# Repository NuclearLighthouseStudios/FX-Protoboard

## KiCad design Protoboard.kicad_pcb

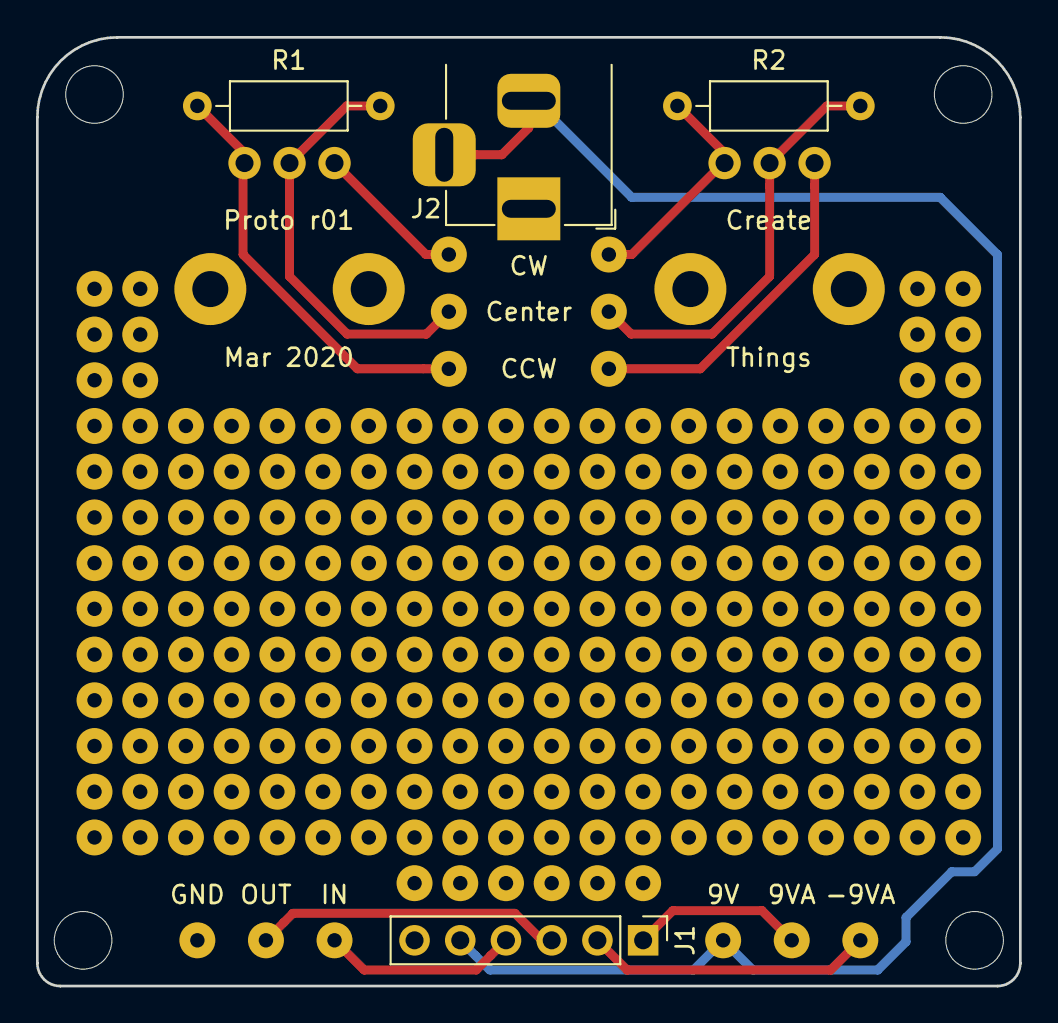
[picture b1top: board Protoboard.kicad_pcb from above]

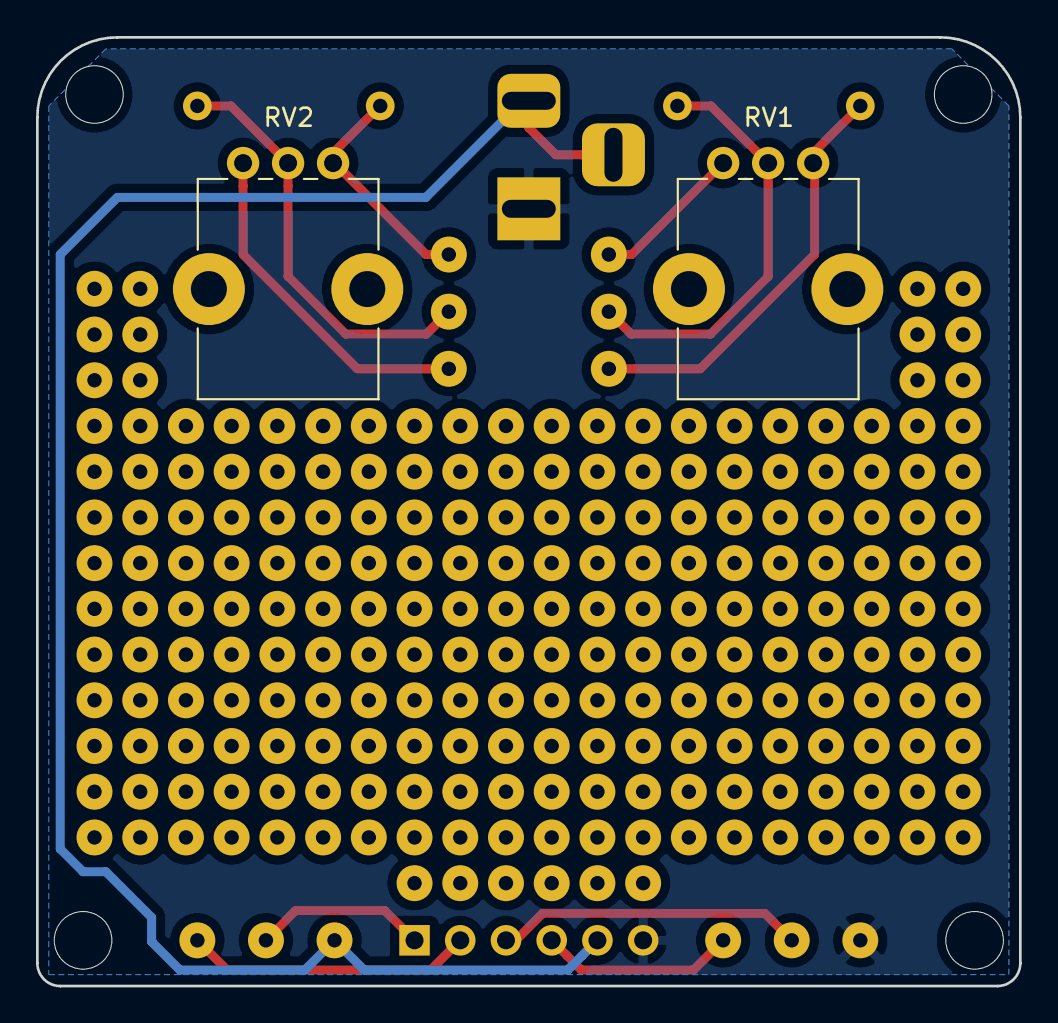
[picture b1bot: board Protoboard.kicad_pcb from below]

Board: 2 copper layers, 54.6 x 52.7 mm, 18 parts (2 on the bottom side), 12 nets.

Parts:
9V, 9VA: TestPoint; SolderWirePad_1x01_Drill0.8mm
-9VA: TestPoint; SolderWirePad_1x01_Drill0.8mm
GND: TestPoint; SolderWirePad_1x01_Drill0.8mm
IN: TestPoint; SolderWirePad_1x01_Drill0.8mm
J1: Conn_01x06_Female; PinHeader_1x06_P2.54mm_Vertical
J2: Barrel_Jack_Switch; BarrelJack_Horizontal_Short
OUT: TestPoint; SolderWirePad_1x01_Drill0.8mm
R1, R2: 39k; R_Axial_DIN0207_L6.3mm_D2.5mm_P10.16mm_Horizontal
RV1, RV2: 100k; Potentiometer_Alps_RK09K_Single_Vertical
TP7, TP8, TP9, TP10, TP11, TP12: TestPoint; SolderWirePad_1x01_Drill0.8mm

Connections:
+9V: 9V.1, J1.5, J2.2, J2.3
+9VA: 9VA.1, J1.1
-9VA: -9VA.1, J1.2
GND: GND.1, J1.6, J2.1
Input: IN.1, J1.4
unnamed: R1.1, RV1.2, TP8.1
unnamed: R1.2, RV1.3, TP9.1
unnamed: R2.1, RV2.2, TP11.1
unnamed: R2.2, RV2.3, TP12.1
unnamed: RV1.1, TP7.1
unnamed: RV2.1, TP10.1
Output: J1.3, OUT.1

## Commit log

2020-03-11 Initial Commit!

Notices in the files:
Protoboard.kicad_pcb:
CC BY-SA
